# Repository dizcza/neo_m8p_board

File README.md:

# ublox NEO-M8P GPS Board design

The board serves an SMA connector for an external active antenna and a slot for a passive ceramic patch antenna 25x25 mm.

## Schematics

[schematics.pdf](schematics.pdf)

## 3D rendered

<table style="width:100%">
	<tr>
		<th>Top view</th>
		<th>Bottom view</th>
	<tr>
    <tr>
        <td>
            
        </td>
        <td>
            
        </td>
    </tr>
</table>

## PCB layout

## Gerber files

See the [gerbers](gerbers) folder.

## Revisions

### V2

SMA active antenna only.

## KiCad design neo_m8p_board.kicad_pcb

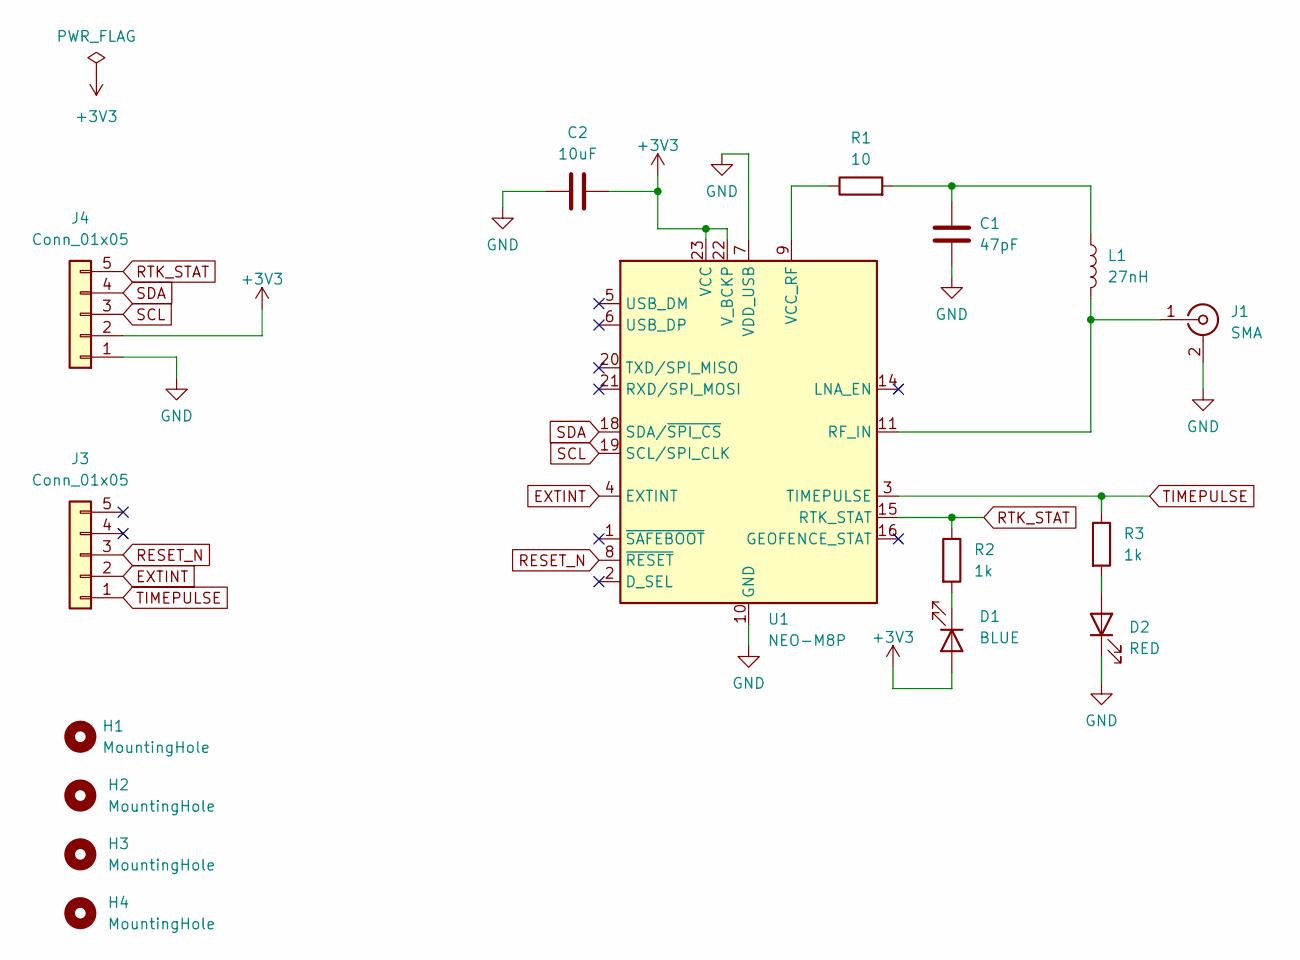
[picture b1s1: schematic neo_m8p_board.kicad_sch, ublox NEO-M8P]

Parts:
C1: 47pF; C_0805_2012Metric_Pad1.18x1.45mm_HandSolder
C2: 10uF; C_0805_2012Metric_Pad1.18x1.45mm_HandSolder; LCSC C15850
D1: BLUE; LED_0805_2012Metric_Pad1.15x1.40mm_HandSolder; LCSC C34499
D2: RED; LED_0805_2012Metric_Pad1.15x1.40mm_HandSolder; LCSC C2286
H1, H2, H3, H4: MountingHole; MountingHole_3.2mm_M3
J1: SMA; SMA_Amphenol_901-143_Horizontal
J3, J4: Conn_01x05; PinHeader_1x05_P2.54mm_Vertical
L1: 27nH; L_0805_2012Metric_Pad1.05x1.20mm_HandSolder
R1: 10; R_0805_2012Metric_Pad1.20x1.40mm_HandSolder
R2, R3: 1k; R_0805_2012Metric_Pad1.20x1.40mm_HandSolder; LCSC C17513
U1: NEO-M8P; ublox_NEO

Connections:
+3V3: C2.2, D1.2 (A), J4.2, U1.22 (V_BCKP), U1.23 (VCC)
EXTINT: J3.2, U1.4 (EXTINT)
GND: C1.2, C2.1, D2.1 (K), J1.2 (Ext), J4.1, U1.7 (VDD_USB), U1.10 (GND), U1.12 (GND), U1.13 (GND), U1.24 (GND)
unnamed: C1.1, L1.1, R1.2
unnamed: D1.1 (K), R2.2
unnamed: D2.2 (A), R3.2
unnamed: J1.1 (In), L1.2, U1.11 (RF_IN)
unnamed: R1.1, U1.9 (VCC_RF)
RESET_N: J3.3, U1.8 (~RESET)
RTK_STAT: J4.5, R2.1, U1.15 (RTK_STAT)
SCL: J4.3, U1.19 (SCL/SPI_CLK)
SDA: J4.4, U1.18 (SDA/~SPI_CS)
TIMEPULSE: J3.1, R3.1, U1.3 (TIMEPULSE)

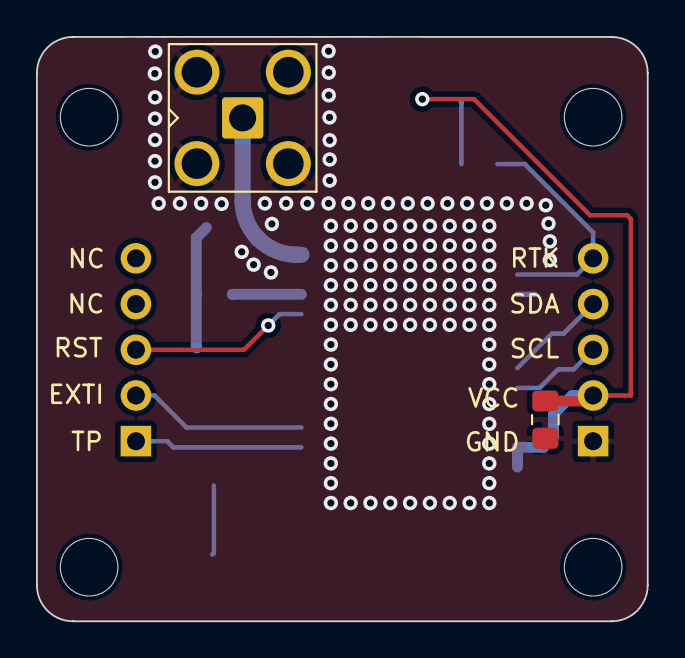
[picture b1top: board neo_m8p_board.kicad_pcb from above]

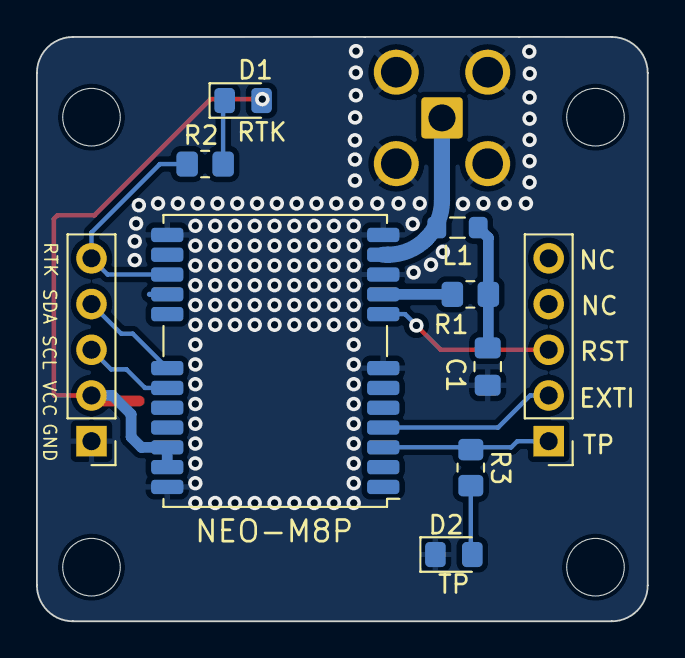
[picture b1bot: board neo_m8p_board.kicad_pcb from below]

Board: 2 copper layers, 33.9 x 32.5 mm, 16 parts (10 on the bottom side), 13 nets.

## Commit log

2023-12-28 completed
2024-01-23 v2: sma antenna only
